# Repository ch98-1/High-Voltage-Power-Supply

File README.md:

# High Voltage Power Supply
High voltage power supply for main capacitor and igniter for PPT systems

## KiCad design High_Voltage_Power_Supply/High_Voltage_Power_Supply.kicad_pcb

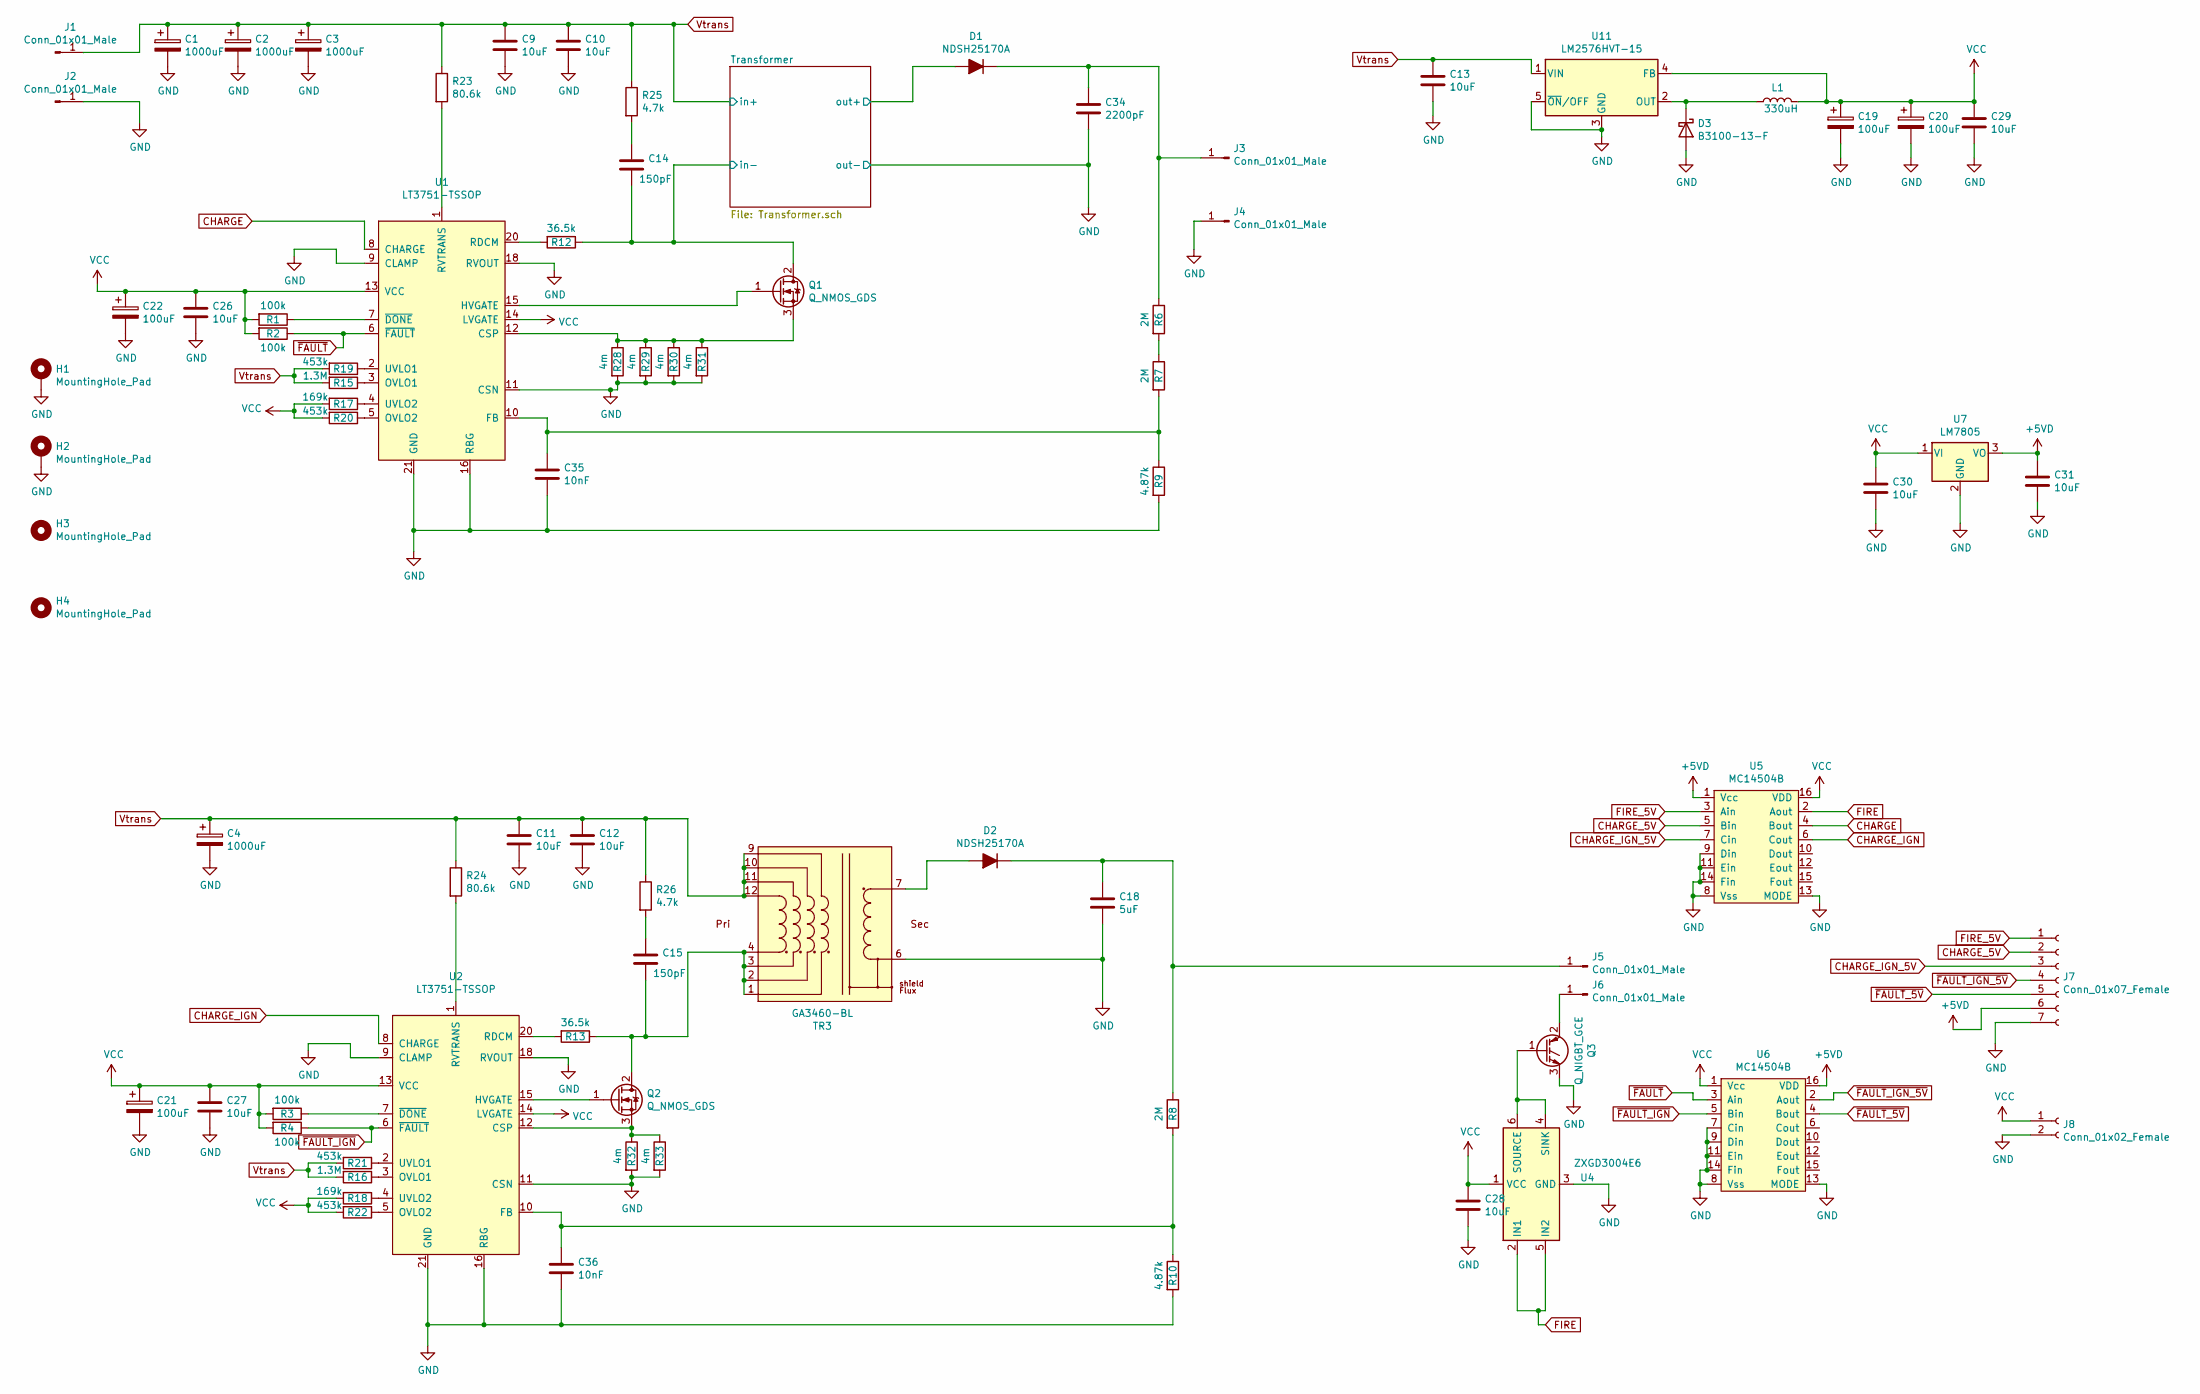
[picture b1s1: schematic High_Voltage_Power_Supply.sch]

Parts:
C1, C2, C3, C4: 1000uF; CP_Radial_D18.0mm_P7.50mm
C9, C10, C11, C12, C13: 10uF; C_1210_3225Metric; Voltage >100V
C14, C15: 150pF; C_1206_3216Metric
C18: 5uF; C_Rect_L31.5mm_W20.0mm_P27.50mm_MKS4; Voltage >600V
C19, C20, C21, C22: 100uF; CP_Radial_D8.0mm_P5.00mm
C26, C27, C28, C29, C30, C31: 10uF; C_1206_3216Metric; Voltage >50V
C34: 2200pF; C_1812_4532Metric; Voltage >1200V
C35, C36: 10nF; C_0603_1608Metric
D1, D2: NDSH25170A; TO-247-2_Vertical
D3: B3100-13-F; D_SMC
H1, H2: MountingHole_Pad; MountingHole_3.2mm_M3_Pad_Via
H3, H4: MountingHole_Pad; MountingHole_3.2mm_M3
J1, J2, J3, J4, J5, J6: Conn_01x01_Male; Banana_Jack_1Pin
J7: Conn_01x07_Female; PinHeader_1x07_P2.54mm_Vertical
J8: Conn_01x02_Female; PinHeader_1x02_P2.54mm_Vertical
L1: 330uH; 60B334C
Q1, Q2: Q_NMOS_GDS; TO-264-3_Vertical; Voltage 200V
Q3: Q_NIGBT_GCE; TO-247-3_Vertical; Voltage >600V
R1, R2, R3, R4: 100k; R_0603_1608Metric
R6, R7, R8: 2M; R_1206_3216Metric
R9, R10: 4.87k; R_1206_3216Metric
R12, R13: 36.5k; R_0603_1608Metric
R15, R16: 1.3M; R_0805_2012Metric
R17, R18: 169k; R_0805_2012Metric
R19, R20, R21, R22: 453k; R_0805_2012Metric
R23, R24: 80.6k; R_0603_1608Metric
R25, R26: 4.7k; R_1206_3216Metric
R28, R29, R30, R31, R32, R33: 4m; R_2512_6332Metric
TR3: GA3460-BL; Transformer_Coilcraft_GA3460-BL
U1, U2: LT3751-TSSOP; HTSSOP-20-1EP_4.4x6.5mm_P0.65mm_EP3.4x6.5mm_ThermalVias
U4: ZXGD3004E6; SOT-23-6
U5, U6: MC14504B; SOIC-16_3.9x9.9mm_P1.27mm
U7: LM7805; SOT-223-3_TabPin2
U11: LM2576HVT-15; TO-220-5_Vertical

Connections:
+5VD: C31.1, J7.6, U5.1 (Vcc), U6.16 (VDD), U7.3 (VO)
/Transformer/in-: C14.2, Q1.2 (D), R12.1; also elsewhere on the board
/Transformer/out+: D1.2 (A); also elsewhere on the board
CHARGE: U1.8 (CHARGE), U5.4 (Bout)
CHARGE_5V: J7.2, U5.5 (Bin)
CHARGE_IGN: U2.8 (CHARGE), U5.6 (Cout)
CHARGE_IGN_5V: J7.3, U5.7 (Cin)
FIRE: U4.2 (IN1), U4.5 (IN2), U5.2 (Aout)
FIRE_5V: J7.1, U5.3 (Ain)
GND: C1.2, C2.2, C3.2, C4.2, C9.2, C10.2, C11.2, C12.2, C13.2, C18.2, C19.2, C20.2, C21.2, C22.2, C26.2, C27.2, C28.2, C29.2, C30.2, C31.2, C34.2, C35.2, C36.2, D3.2 (A), H1.1, H2.1, J2.1, J4.1, J7.7, J8.2, Q3.3 (E), R9.2, R10.2, R28.2, R29.2, R30.2, R31.2, R32.2, R33.2, TR3.6, U1.9 (CLAMP), U1.11 (CSN), U1.16 (RBG), U1.18 (RVOUT), U1.21 (GND), U2.9 (CLAMP), U2.11 (CSN), U2.16 (RBG), U2.18 (RVOUT), U2.21 (GND), U4.3 (GND), U5.8 (Vss), U5.9 (Din), U5.11 (Ein), U5.13 (MODE), U5.14 (Fin), U6.7 (Cin), U6.8 (Vss), U6.9 (Din), U6.11 (Ein), U6.13 (MODE), U6.14 (Fin), U7.2 (GND), U11.3 (GND), U11.5 (~ON~/OFF); also elsewhere on the board
unnamed: C14.1, R25.2
unnamed: C15.1, R26.2
unnamed: C15.2, Q2.2 (D), R13.1, TR3.1, TR3.2, TR3.3, TR3.4
unnamed: C18.1, D2.1 (K), J5.1, R8.1
unnamed: C34.1, D1.1 (K), J3.1, R6.1
unnamed: C35.1, R7.2, R9.1, U1.10 (FB)
unnamed: C36.1, R8.2, R10.1, U2.10 (FB)
unnamed: D2.2 (A), TR3.7
unnamed: D3.1 (K), L1.1, U11.2 (OUT)
unnamed: J6.1, Q3.2 (C)
unnamed: Q1.1 (G), U1.15 (HVGATE)
unnamed: Q1.3 (S), R28.1, R29.1, R30.1, R31.1, U1.12 (CSP)
unnamed: Q2.1 (G), U2.15 (HVGATE)
unnamed: Q2.3 (S), R32.1, R33.1, U2.12 (CSP)
unnamed: Q3.1 (G), U4.4 (SINK), U4.6 (SOURCE)
unnamed: R1.1, U1.7 (~DONE~)
unnamed: R3.1, U2.7 (~DONE~)
unnamed: R6.2, R7.1
unnamed: R12.2, U1.20 (RDCM)
unnamed: R13.2, U2.20 (RDCM)
unnamed: R15.1, U1.3 (OVLO1)
unnamed: R16.1, U2.3 (OVLO1)
unnamed: R17.1, U1.4 (UVLO2)
unnamed: R18.1, U2.4 (UVLO2)
unnamed: R19.1, U1.2 (UVLO1)
unnamed: R20.1, U1.5 (OVLO2)
unnamed: R21.1, U2.2 (UVLO1)
unnamed: R22.1, U2.5 (OVLO2)
unnamed: R23.2, U1.1 (RVTRANS)
unnamed: R24.2, U2.1 (RVTRANS)
VCC: C19.1, C20.1, C21.1, C22.1, C26.1, C27.1, C28.1, C29.1, C30.1, J8.1, L1.2, R1.2, R2.2, R3.2, R4.2, R17.2, R18.2, R20.2, R22.2, U1.13 (VCC), U1.14 (LVGATE), U2.13 (VCC), U2.14 (LVGATE), U4.1 (VCC), U5.16 (VDD), U6.1 (Vcc), U7.1 (VI), U11.4 (FB)
Vtrans: C1.1, C2.1, C3.1, C4.1, C9.1, C10.1, C11.1, C12.1, C13.1, J1.1, R15.2, R16.2, R19.2, R21.2, R23.1, R24.1, R25.1, R26.1, TR3.9, TR3.10, TR3.11, TR3.12, U11.1 (VIN); also elsewhere on the board
~FAULT_5V~: J7.5, U6.4 (Bout)
~FAULT_IGN_5V~: J7.4, U6.2 (Aout)
~FAULT_IGN~: R4.1, U2.6 (~FAULT~), U6.5 (Bin)
~FAULT~: R2.1, U1.6 (~FAULT~), U6.3 (Ain)

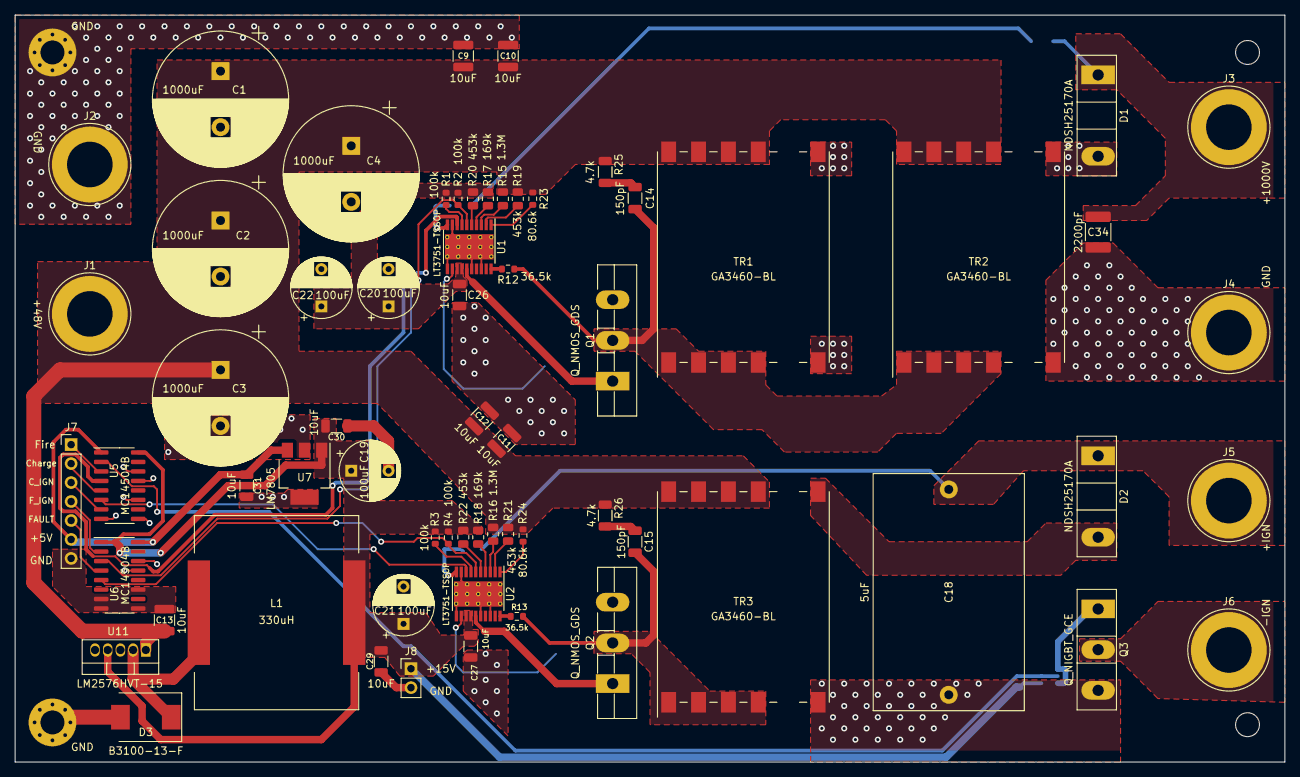
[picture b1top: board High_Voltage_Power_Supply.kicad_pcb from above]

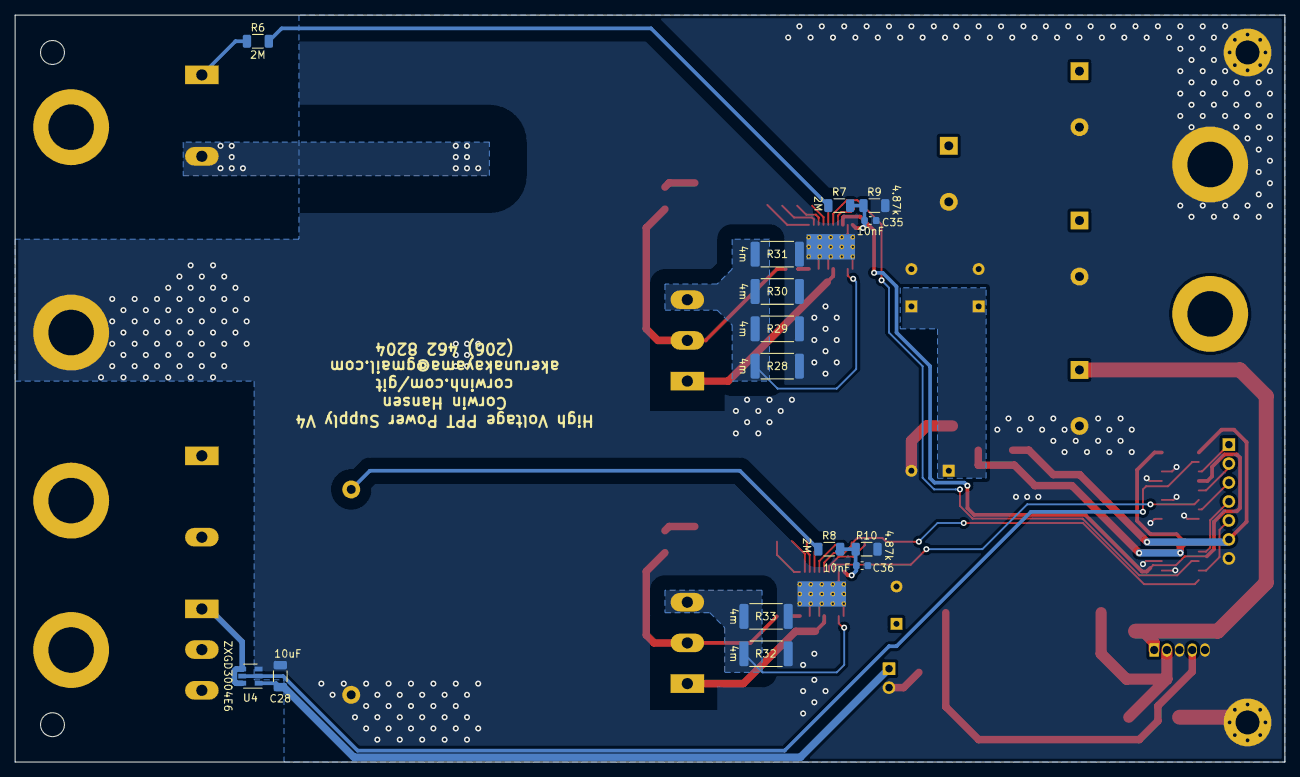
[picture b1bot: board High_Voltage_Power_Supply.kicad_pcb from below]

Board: 2 copper layers, 170.0 x 100.0 mm, 83 parts (15 on the bottom side), 46 nets.

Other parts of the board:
TR1, TR2: GA3460-BL; Transformer_Coilcraft_GA3460-BL

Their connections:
/Transformer/in-: TR1.1, TR1.2, TR1.3, TR1.4, TR2.1, TR2.2, TR2.3, TR2.4; also elsewhere on the board
/Transformer/out+: TR1.7, TR2.7; also elsewhere on the board
GND: TR1.6, TR2.6; also elsewhere on the board
Vtrans: TR1.9, TR1.10, TR1.11, TR1.12, TR2.9, TR2.10, TR2.11, TR2.12; also elsewhere on the board

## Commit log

2018-08-30 Added project files and license
2018-08-31 Finished basic power supply schematic
2018-08-31 Centered schematic
2019-02-21 Added schimatic PDF
2020-07-11 Updated readme and license
2020-07-11 Removed some unnecessary files
2020-08-05 More basic component updates
2020-08-08 Finalised the schematic and BOM
2020-08-08 Started on the PCB
2020-08-14 Finished most of the PCB layout
2020-08-14 Added Done and Fault outputs
2020-08-15 Updated text location
2020-08-15 removed unnecessary files
2020-08-19 Started on LTspice simulation file for the circuit
2020-08-21 minor pcb update
2020-08-21 updated pcb
2020-08-26 Added some notes for it
2020-08-26 Fixed the order qualtity mistake
2020-09-05 modified PCB to have all the silkscreen text visible
2020-09-05 Removed a via in the wrong position
2020-09-16 updated simulation with 2 transformer design
2020-10-01 Updated schematic to run on regulation mode only
2020-10-01 Started PCB layout for new version of the board
2020-10-02 removed unnecessory item from bom
2020-10-03 did more pcb layout
2020-10-03 filled unfilled zones
2020-10-15 Started design of the ignitor circuit
2020-10-18 schematic update
2020-10-28 Finished the v2 of the schematic
2020-10-28 Updated BOM
2020-10-29 pcb fully layed out
2020-10-29 Layout update for minor labling issues
2020-10-29 more layout update
2020-10-29 added labels on pins
2020-11-12 made small adjustments to pcb to clean it up a bit
2020-11-12 more change with vias
2020-11-14 updated text to be right way around
2020-11-17 pin labling error fixed and arduino project for testing added
2020-11-17 finishe dthe basic test code
2020-11-17 added more test codes
2021-04-23 Created V3 of the schematic
2021-04-27 schematic update with mounting holes
2021-05-25 added new components and replaced out of stock ones in BOM
2021-05-27 Edited schematic to use new buck converter chip.
2021-06-15 Rough component placements to allow heat sinks to be installed
2021-06-19 routed most of the components on pcb
2021-06-19 more work on pcb routuing
2021-06-22 traces fully laid out
2021-06-22 labeled components
2021-06-22 updated silkscreen labeling
2021-06-25 minor update to labeling for pcb
2021-06-26 Minor layout change
2021-06-26 added more labeling
2021-06-26 Mirrored the text on the back
2021-06-26 updated pcb view
2021-07-20 minor fix on vias not connected to anything
2021-07-20 Minor bom and text change
2021-07-20 More bom update
2021-07-28 Updated component list and schematic for v4
2021-07-28 updated label text
2021-09-02 Component updates for new version
2021-09-04 updated components to match new requirements from experiments
2021-12-09 finished pcb v4 layout. Added cad for heatsink.
2021-12-09 cleaned up heat sink cad
2021-12-10 minor layout update
2021-12-11 minor updates on vias
2021-12-11 fixed some issues
